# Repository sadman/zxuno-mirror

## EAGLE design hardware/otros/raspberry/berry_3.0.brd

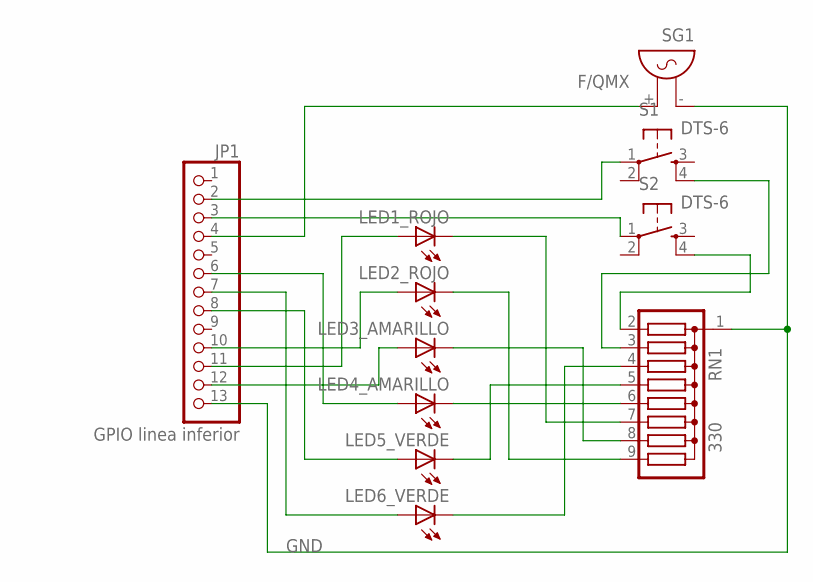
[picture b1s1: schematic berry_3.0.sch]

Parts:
JP1: GPIO linea inferior; 1X13
LED1_ROJO, LED2_ROJO, LED3_AMARILLO, LED4_AMARILLO, LED5_VERDE, LED6_VERDE: LED5MM
RN1: 330; SIL9
S1, S2: DTS-6
SG1: F/QMX

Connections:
GND: JP1.13, RN1.1, SG1.- (1)
unnamed: LED5_VERDE.K (C), RN1.5
unnamed: JP1.2, S1.1
unnamed: LED3_AMARILLO.K (C), RN1.8
unnamed: JP1.10, LED2_ROJO.A
unnamed: LED4_AMARILLO.K (C), RN1.6
unnamed: LED2_ROJO.K (C), RN1.9
unnamed: JP1.4, SG1.+ (2)
unnamed: LED1_ROJO.K (C), RN1.7
unnamed: LED6_VERDE.K (C), RN1.4
unnamed: JP1.7, LED6_VERDE.A
unnamed: JP1.8, LED5_VERDE.A
unnamed: RN1.2, S2.4
unnamed: RN1.3, S1.4
unnamed: JP1.11, LED1_ROJO.A
unnamed: JP1.3, S2.1
unnamed: JP1.6, LED4_AMARILLO.A
unnamed: JP1.12, LED3_AMARILLO.A

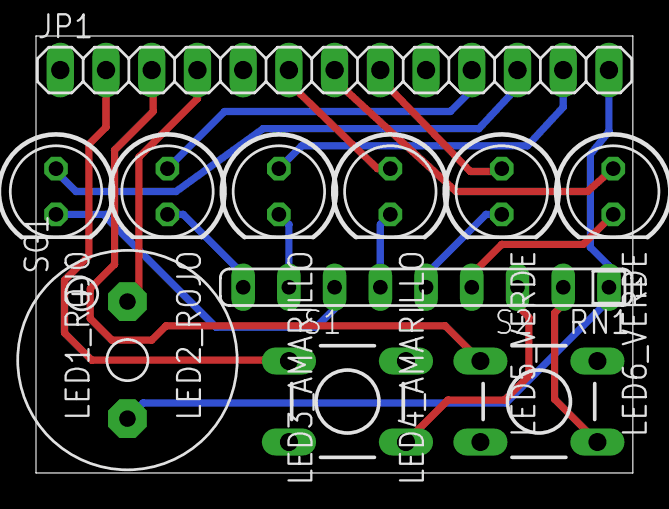
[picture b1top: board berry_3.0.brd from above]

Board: 2 copper layers, 33.2 x 24.3 mm, 11 parts (0 on the bottom side), 18 nets.

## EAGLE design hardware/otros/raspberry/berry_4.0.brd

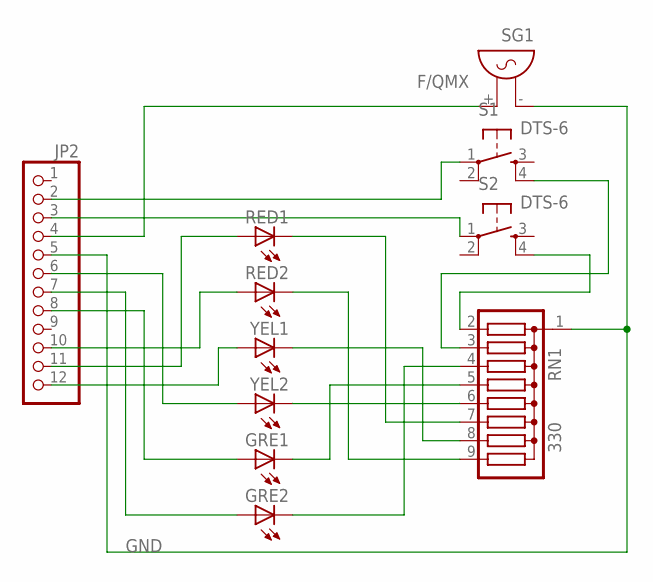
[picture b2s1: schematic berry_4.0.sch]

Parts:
GRE1, GRE2: LED3MM
JP2: PINHD-1X12; 1X12
RED1, RED2: LED3MM
RN1: 330; SIL9
S1, S2: DTS-6
SG1: F/QMX
YEL1, YEL2: LED3MM

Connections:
GND: JP2.5, RN1.1, SG1.- (1)
unnamed: GRE1.K (C), RN1.5
unnamed: JP2.2, S1.1
unnamed: RN1.8, YEL1.K (C)
unnamed: JP2.10, RED2.A
unnamed: RN1.6, YEL2.K (C)
unnamed: RED2.K (C), RN1.9
unnamed: JP2.4, SG1.+ (2)
unnamed: RED1.K (C), RN1.7
unnamed: GRE2.K (C), RN1.4
unnamed: GRE2.A, JP2.7
unnamed: GRE1.A, JP2.8
unnamed: RN1.2, S2.4
unnamed: RN1.3, S1.4
unnamed: JP2.11, RED1.A
unnamed: JP2.3, S2.1
unnamed: JP2.6, YEL2.A
unnamed: JP2.12, YEL1.A

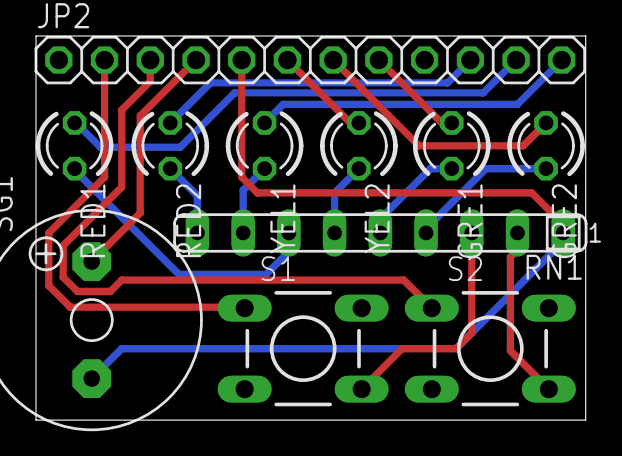
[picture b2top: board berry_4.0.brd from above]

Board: 2 copper layers, 30.5 x 21.3 mm, 11 parts (0 on the bottom side), 18 nets.

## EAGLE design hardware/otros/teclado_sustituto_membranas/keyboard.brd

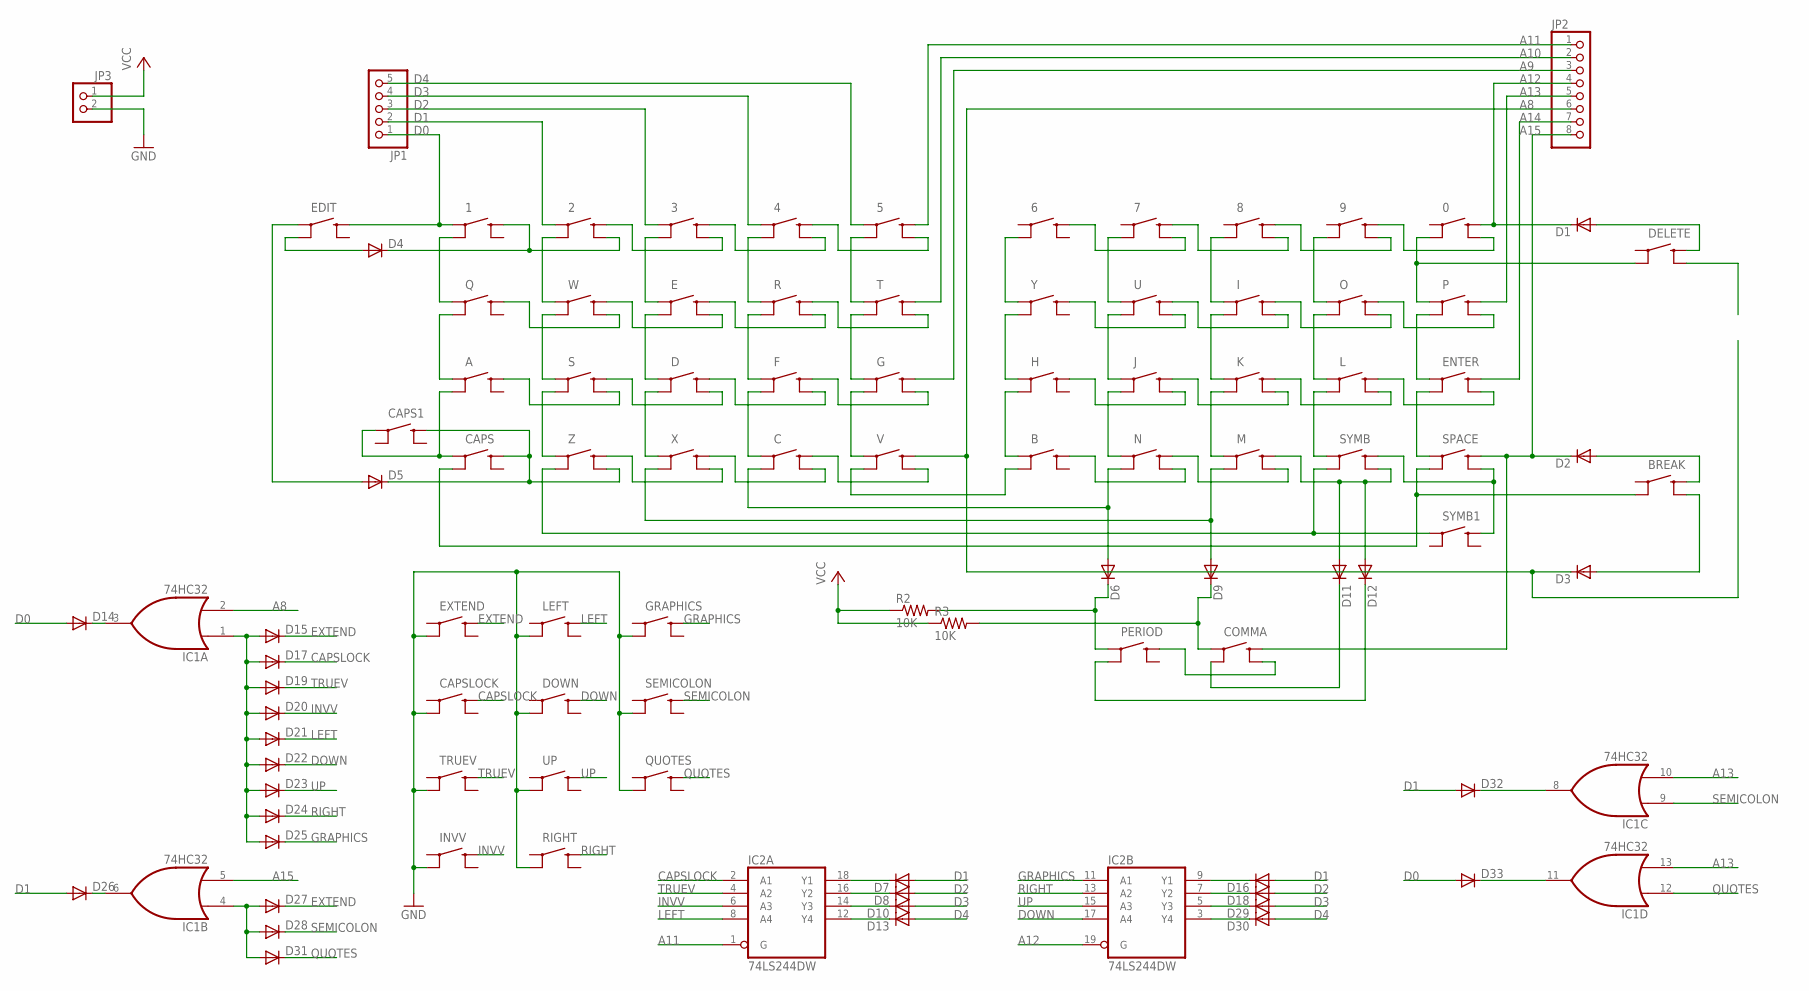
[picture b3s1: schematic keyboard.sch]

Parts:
0, 1, 2, 3, 4, 5, 6, 7, 8, 9: SWITCH-MOMENTARY-2SMD; TACTILE-SWITCH-SMD
A: SWITCH-MOMENTARY-2SMD; TACTILE-SWITCH-SMD
B: SWITCH-MOMENTARY-2SMD; TACTILE-SWITCH-SMD
BREAK: SWITCH-MOMENTARY-2SMD; TACTILE-SWITCH-SMD
C: SWITCH-MOMENTARY-2SMD; TACTILE-SWITCH-SMD
CAPS, CAPS1: SWITCH-MOMENTARY-2SMD; TACTILE-SWITCH-SMD
CAPSLOCK: SWITCH-MOMENTARY-2SMD; TACTILE-SWITCH-SMD
COMMA: SWITCH-MOMENTARY-2SMD; TACTILE-SWITCH-SMD
D: SWITCH-MOMENTARY-2SMD; TACTILE-SWITCH-SMD
D1, D2, D3, D4, D5, D6, D7, D8, D9, D10, D11, D12, D13, D14, D15, D16, D17, D18, D19, D20, D21, D22, D23, D24, D25, D26, D27, D28, D29, D30, D31, D32, D33: DIODE-SOD323-R; SOD323-R
DELETE: SWITCH-MOMENTARY-2SMD; TACTILE-SWITCH-SMD
DOWN: SWITCH-MOMENTARY-2SMD; TACTILE-SWITCH-SMD
E: SWITCH-MOMENTARY-2SMD; TACTILE-SWITCH-SMD
EDIT: SWITCH-MOMENTARY-2SMD; TACTILE-SWITCH-SMD
ENTER: SWITCH-MOMENTARY-2SMD; TACTILE-SWITCH-SMD
EXTEND: SWITCH-MOMENTARY-2SMD; TACTILE-SWITCH-SMD
F: SWITCH-MOMENTARY-2SMD; TACTILE-SWITCH-SMD
G: SWITCH-MOMENTARY-2SMD; TACTILE-SWITCH-SMD
GRAPHICS: SWITCH-MOMENTARY-2SMD; TACTILE-SWITCH-SMD
H: SWITCH-MOMENTARY-2SMD; TACTILE-SWITCH-SMD
I: SWITCH-MOMENTARY-2SMD; TACTILE-SWITCH-SMD
IC1: 74HC32; SO14
IC2: 74LS244DW; SO20W
INVV: SWITCH-MOMENTARY-2SMD; TACTILE-SWITCH-SMD
J: SWITCH-MOMENTARY-2SMD; TACTILE-SWITCH-SMD
JP1: PINHD-1X5; 1X05
JP2: PINHD-1X8; 1X08
JP3: PINHD-1X2; 1X02
K: SWITCH-MOMENTARY-2SMD; TACTILE-SWITCH-SMD
L: SWITCH-MOMENTARY-2SMD; TACTILE-SWITCH-SMD
LEFT: SWITCH-MOMENTARY-2SMD; TACTILE-SWITCH-SMD
M: SWITCH-MOMENTARY-2SMD; TACTILE-SWITCH-SMD
N: SWITCH-MOMENTARY-2SMD; TACTILE-SWITCH-SMD
O: SWITCH-MOMENTARY-2SMD; TACTILE-SWITCH-SMD
P: SWITCH-MOMENTARY-2SMD; TACTILE-SWITCH-SMD
PERIOD: SWITCH-MOMENTARY-2SMD; TACTILE-SWITCH-SMD
Q: SWITCH-MOMENTARY-2SMD; TACTILE-SWITCH-SMD
QUOTES: SWITCH-MOMENTARY-2SMD; TACTILE-SWITCH-SMD
R: SWITCH-MOMENTARY-2SMD; TACTILE-SWITCH-SMD
R2, R3: 10K; M0805
RIGHT: SWITCH-MOMENTARY-2SMD; TACTILE-SWITCH-SMD
S: SWITCH-MOMENTARY-2SMD; TACTILE-SWITCH-SMD
SEMICOLON: SWITCH-MOMENTARY-2SMD; TACTILE-SWITCH-SMD
SPACE: SWITCH-MOMENTARY-2SMD; TACTILE-SWITCH-SMD
SYMB, SYMB1: SWITCH-MOMENTARY-2SMD; TACTILE-SWITCH-SMD
T: SWITCH-MOMENTARY-2SMD; TACTILE-SWITCH-SMD
TRUEV: SWITCH-MOMENTARY-2SMD; TACTILE-SWITCH-SMD
U: SWITCH-MOMENTARY-2SMD; TACTILE-SWITCH-SMD
UP: SWITCH-MOMENTARY-2SMD; TACTILE-SWITCH-SMD
V: SWITCH-MOMENTARY-2SMD; TACTILE-SWITCH-SMD
W: SWITCH-MOMENTARY-2SMD; TACTILE-SWITCH-SMD
X: SWITCH-MOMENTARY-2SMD; TACTILE-SWITCH-SMD
Y: SWITCH-MOMENTARY-2SMD; TACTILE-SWITCH-SMD
Z: SWITCH-MOMENTARY-2SMD; TACTILE-SWITCH-SMD

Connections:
A8: D3.C, IC1.2 (I1), JP2.6, V.3 (2)
A9: G.3 (2), JP2.3
A10: JP2.2, T.3 (2)
A11: 5.3 (2), IC2.1 (G), JP2.1
A12: 0.3 (2), D1.C, IC2.19 (G), JP2.4
A13: IC1.10 (I1), IC1.13 (I1), JP2.5, P.3 (2)
A14: ENTER.3 (2), JP2.7
A15: COMMA.3 (2), D2.C, IC1.5 (I1), JP2.8, SPACE.3 (2)
CAPSLOCK: CAPSLOCK.3 (2), D17.C, IC2.2 (A1)
D0: 1.1, D14.A, D33.A, EDIT.3 (2), JP1.1
D1: 2.1, D7.A, D16.A, D26.A, D32.A, JP1.2
D2: 3.1, D8.A, D18.A, JP1.3
D3: 4.1, D10.A, D29.A, JP1.4
D4: 5.1, D13.A, D30.A, JP1.5
DOWN: D22.C, DOWN.3 (2), IC2.17 (A4)
EXTEND: D15.C, D27.C, EXTEND.3 (2)
GND: CAPSLOCK.2 (3), DOWN.2 (3), EXTEND.2 (3), GRAPHICS.2 (3), IC1.7 (GND), IC2.10 (GND), INVV.2 (3), JP3.2, LEFT.2 (3), QUOTES.2 (3), RIGHT.2 (3), SEMICOLON.2 (3), TRUEV.2 (3), UP.2 (3)
GRAPHICS: D25.C, GRAPHICS.3 (2), IC2.11 (A1)
INVV: D20.C, IC2.6 (A3), INVV.3 (2)
LEFT: D21.C, IC2.8 (A4), LEFT.3 (2)
unnamed: D4.A, EDIT.2 (3)
unnamed: D5.A, EDIT.1
unnamed: BREAK.3 (2), D2.A
unnamed: BREAK.4, D3.A
unnamed: D1.A, DELETE.3 (2)
unnamed: 1.2 (3), Q.1
unnamed: A.1, Q.2 (3)
unnamed: A.2 (3), CAPS.1, CAPS1.1
unnamed: BREAK.2 (3), CAPS.2 (3), SPACE.2 (3)
unnamed: B.1, H.2 (3)
unnamed: H.1, Y.2 (3)
unnamed: 6.2 (3), Y.1
unnamed: 2.2 (3), W.1
unnamed: S.1, W.2 (3)
unnamed: S.2 (3), Z.1
unnamed: SYMB.2 (3), SYMB1.1, Z.2 (3)
unnamed: D9.A, M.2 (3), X.2 (3)
unnamed: C.2 (3), D6.A, N.2 (3)
unnamed: B.2 (3), V.2 (3)
unnamed: 3.2 (3), E.1
unnamed: D.1, E.2 (3)
unnamed: D.2 (3), X.1
unnamed: 4.2 (3), R.1
unnamed: F.1, R.2 (3)
unnamed: C.1, F.2 (3)
unnamed: 5.2 (3), T.1
unnamed: G.1, T.2 (3)
unnamed: G.2 (3), V.1
unnamed: 3.3 (2), 4.4
unnamed: 4.3 (2), 5.4
unnamed: 2.3 (2), 3.4
unnamed: 1.3 (2), 2.4, D4.C
unnamed: C.3 (2), V.4
unnamed: R.3 (2), T.4
unnamed: E.3 (2), R.4
unnamed: E.4, W.3 (2)
unnamed: Q.3 (2), W.4
unnamed: F.3 (2), G.4
unnamed: D.3 (2), F.4
unnamed: D.4, S.3 (2)
unnamed: A.3 (2), S.4
unnamed: 0.4, 9.3 (2)
unnamed: J.2 (3), N.1
unnamed: J.1, U.2 (3)
unnamed: 7.2 (3), U.1
unnamed: K.2 (3), M.1
unnamed: I.2 (3), K.1
unnamed: 8.2 (3), I.1
unnamed: L.2 (3), SYMB.1
unnamed: L.1, O.2 (3)
unnamed: 9.2 (3), O.1
unnamed: ENTER.2 (3), SPACE.1
unnamed: ENTER.1, P.2 (3)
unnamed: 0.2 (3), DELETE.2 (3), P.1
unnamed: 8.3 (2), 9.4
unnamed: 7.3 (2), 8.4
unnamed: 6.3 (2), 7.4
unnamed: C.4, X.3 (2)
unnamed: X.4, Z.3 (2)
unnamed: CAPS.3 (2), CAPS1.3 (2), D5.C, Z.4
unnamed: O.3 (2), P.4
unnamed: I.3 (2), O.4
unnamed: I.4, U.3 (2)
unnamed: U.4, Y.3 (2)
unnamed: ENTER.4, L.3 (2)
unnamed: K.3 (2), L.4
unnamed: J.3 (2), K.4
unnamed: H.3 (2), J.4
unnamed: SPACE.4, SYMB.3 (2), SYMB1.3 (2)
unnamed: D11.A, D12.A, M.3 (2), SYMB.4
unnamed: M.4, N.3 (2)
unnamed: B.3 (2), N.4
unnamed: D7.C, IC2.18 (Y1)
unnamed: D8.C, IC2.16 (Y2)
unnamed: COMMA.4, PERIOD.3 (2)
unnamed: D10.C, IC2.14 (Y3)
unnamed: COMMA.2 (3), D11.C
unnamed: D12.C, PERIOD.2 (3)
unnamed: D13.C, IC2.12 (Y4)
unnamed: D16.C, IC2.9 (Y1)
unnamed: D6.C, PERIOD.1, R2.2
unnamed: COMMA.1, D9.C, R3.2
unnamed: D14.C, IC1.3 (O)
unnamed: D18.C, IC2.7 (Y2)
unnamed: D26.C, IC1.6 (O)
unnamed: D27.A, D28.A, D31.A, IC1.4 (I0)
unnamed: D29.C, IC2.5 (Y3)
unnamed: D30.C, IC2.3 (Y4)
unnamed: D15.A, D17.A, D19.A, D20.A, D21.A, D22.A, D23.A, D24.A, D25.A, IC1.1 (I0)
unnamed: D32.C, IC1.8 (O)
unnamed: D33.C, IC1.11 (O)
QUOTES: D31.C, IC1.12 (I0), QUOTES.3 (2)
RIGHT: D24.C, IC2.13 (A2), RIGHT.3 (2)
SEMICOLON: D28.C, IC1.9 (I0), SEMICOLON.3 (2)
TRUEV: D19.C, IC2.4 (A2), TRUEV.3 (2)
UP: D23.C, IC2.15 (A3), UP.3 (2)
VCC: IC1.14 (VCC), IC2.20 (VCC), JP3.1, R2.1, R3.1

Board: 2 copper layers, 98 parts (58 on the bottom side), 117 nets, no tracks yet.

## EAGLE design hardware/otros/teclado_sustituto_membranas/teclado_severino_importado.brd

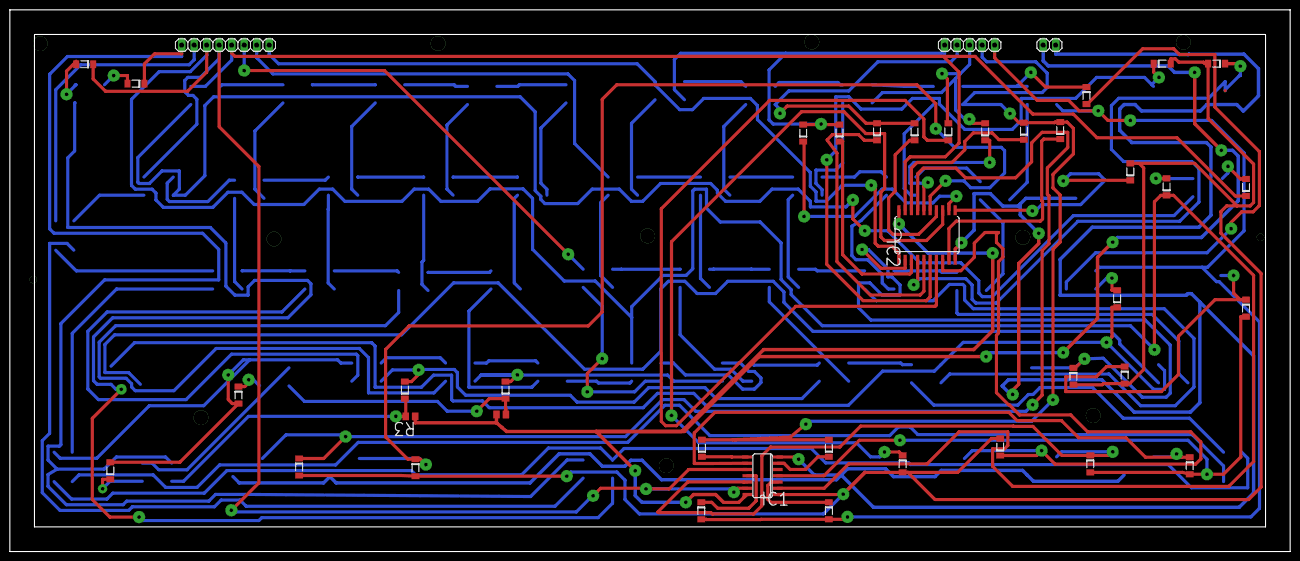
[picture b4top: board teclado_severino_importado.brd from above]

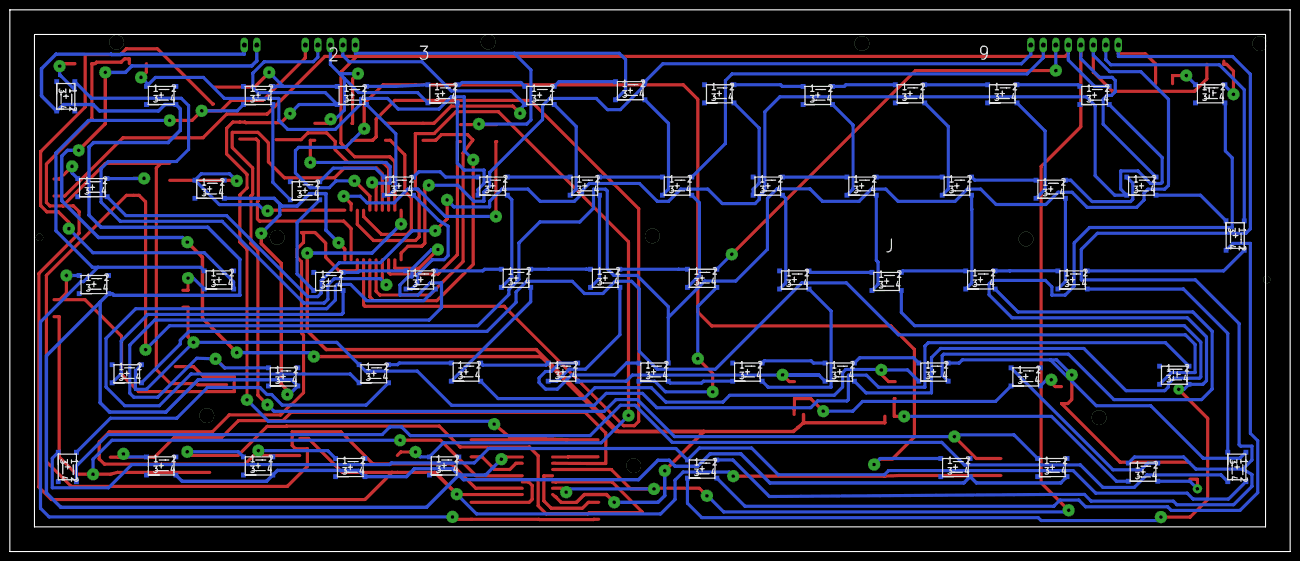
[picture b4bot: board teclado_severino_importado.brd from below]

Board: 2 copper layers, 260.0 x 110.0 mm, 111 parts (58 on the bottom side), 116 nets.

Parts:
0, 1, 2, 3, 4, 5, 6, 7, 8, 9, ._PERIOD_: B3F-40XX_2PRIMARY
,_COMMA_: B3F-40XX_2PRIMARY
A: B3F-40XX_2PRIMARY
B: B3F-40XX_2PRIMARY
BREAK: MINISWITCH_SMD_1PRIMARY
C: B3F-40XX_2PRIMARY
CAPS: MINISWITCH_SMD_1PRIMARY
CAPS1: B3F-40XX_2PRIMARY
CAPSLOCK: B3F-40XX_2PRIMARY
D: B3F-40XX_2PRIMARY
D1, D2, D3, D4, D5, D6, D7, D8, D9, D10, D11, D12, D13, D14, D15, D16, D17, D18, D19, D20, D21, D22, D23, D24, D25, D26, D27, D28, D29, D30, D31, D32, D33: MELF-D3512-1405_1PRIMARY
DELETE: B3F-40XX_2PRIMARY
DEXTRA: MELF-D3512-1405_1PRIMARY
DOWN: B3F-40XX_2PRIMARY
DUMMY1, DUMMY2: P:EX59Y59D591
DUMMY3, DUMMY4, DUMMY5, DUMMY6, DUMMY7, DUMMY8, DUMMY9, DUMMY10, DUMMY11, DUMMY12: P:EX118Y118D1181
E: B3F-40XX_2PRIMARY
EDIT: B3F-40XX_2PRIMARY
ENTER: B3F-40XX_1PRIMARY
EXTEND: B3F-40XX_2PRIMARY
F: B3F-40XX_2PRIMARY
G: B3F-40XX_2PRIMARY
GRAPHICS: B3F-40XX_2PRIMARY
H: B3F-40XX_2PRIMARY
I: B3F-40XX_2PRIMARY
IC1: 74HC32; SO14_1PRIMARY
IC2: 74LS244DW; SO20W_1PRIMARY
INVV: B3F-40XX_2PRIMARY
J: B3F-40XX_2PRIMARY
JP1: 1X05_1PRIMARY
JP2: 1X08_1PRIMARY
JP3: 1X02_1PRIMARY
K: B3F-40XX_2PRIMARY
L: B3F-40XX_2PRIMARY
LEFT: B3F-40XX_2PRIMARY
M: B3F-40XX_2PRIMARY
N: B3F-40XX_2PRIMARY
O: B3F-40XX_2PRIMARY
P: B3F-40XX_2PRIMARY
Q: B3F-40XX_2PRIMARY
QUOTES: B3F-40XX_2PRIMARY
R: B3F-40XX_2PRIMARY
R2, R3: 10K; M0805_1PRIMARY
RIGHT: B3F-40XX_2PRIMARY
S: B3F-40XX_2PRIMARY
SEMICOLON: B3F-40XX_2PRIMARY
SPACE: B3F-40XX_2PRIMARY
SYMB, SYMB1: B3F-40XX_1PRIMARY
T: B3F-40XX_2PRIMARY
TRUEV: B3F-40XX_1PRIMARY
U: B3F-40XX_2PRIMARY
UP: B3F-40XX_2PRIMARY
V: B3F-40XX_2PRIMARY
W: B3F-40XX_2PRIMARY
X: B3F-40XX_2PRIMARY
Y: B3F-40XX_2PRIMARY
Z: B3F-40XX_2PRIMARY

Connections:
A8: D3.2, DEXTRA.2, IC1.2, JP2.6, V.2
A9: G.2, JP2.3
A10: JP2.2, T.2
A11: 5.2, IC2.1, JP2.1
A12: 0.2, D1.2, IC2.19, JP2.4
A13: IC1.10, IC1.13, JP2.5, P.2
A14: ENTER.1, JP2.7
CAPSLOCK: CAPSLOCK.1, D17.2, IC2.2
D0: 1.3, D14.1, D33.1, EDIT.1, JP1.1
D1: 2.3, D7.1, D16.1, D26.1, D32.1, JP1.2
D2: 3.3, D8.1, D18.1, JP1.3
D3: 4.3, D10.1, D29.1, JP1.4
D4: 5.3, D13.1, D30.1, JP1.5
DOWN: D22.2, DOWN.1, IC2.17
EXTEND: D15.2, D27.2, EXTEND.1
GND: CAPSLOCK.4, DOWN.4, EXTEND.4, GRAPHICS.4, IC1.7, IC2.10, INVV.4, JP3.2, LEFT.4, QUOTES.4, RIGHT.4, SEMICOLON.4, TRUEV.4, UP.4
GRAPHICS: D25.2, GRAPHICS.1, IC2.11
INVV: D20.2, IC2.6, INVV.1
LEFT: D21.2, IC2.8, LEFT.1
NET0_1: 0.1, 9.2
NET0_4: 0.4, DELETE.4, P.3
NET1_2: 1.2, 2.1, D4.2
NET1_4: 1.4, Q.3
NET2_2: 2.2, 3.1
NET2_4: 2.4, W.3
NET3_2: 3.2, 4.1
NET3_4: 3.4, E.3
NET4_2: 4.2, 5.1
NET4_4: 4.4, R.3
NET5_4: 5.4, T.3
NET6_2: 6.2, 7.1
NET6_4: 6.4, Y.3
NET7_2: 7.2, 8.1
NET7_4: 7.4, U.3
NET8_2: 8.2, 9.1
NET8_4: 8.4, I.3
NET9_4: 9.4, O.3
NET,_COMMA__2: ,_COMMA_.2, ._PERIOD_.1
NET,_COMMA__3: ,_COMMA_.3, D9.2, R3.2
NET,_COMMA__4: ,_COMMA_.4, D11.2
NET._PERIOD__3: ._PERIOD_.3, D6.2, R2.2
NET._PERIOD__4: ._PERIOD_.4, D12.2
NETA_2: A.2, S.1
NETA_3: A.3, Q.4
NETA_4: A.4, CAPS1.3
NETB_2: B.2, N.1
NETB_3: B.3, V.4
NETB_4: B.4, H.4
NETCAPS1_2: CAPS1.2, Z.1
NETC_1: C.1, X.2
NETC_2: C.2, V.1
NETC_3: C.3, F.4
NETC_4: C.4, D6.1, N.3
NETD1_A: D1.1, DELETE.1
NETD4_A: D4.1, EDIT.4
NETD5_A: D5.1, EDIT.3
NETD7_C: D7.2, IC2.18
NETD8_C: D8.2, IC2.16
NETD9_A: D9.1, M.3, X.4
NETD10_C: D10.2, IC2.14
NETD11_A: D11.1, D12.1, M.2, SYMB.1
NETD13_C: D13.2, IC2.12
NETD14_C: D14.2, IC1.3
NETD15_A: D15.1, D17.1, D19.1, D20.1, D21.1, D22.1, D23.1, D24.1, D25.1, IC1.1
NETD16_C: D16.2, IC2.9
NETD18_C: D18.2, IC2.7
NETD26_C: D26.2, IC1.6
NETD27_A: D27.1, D28.1, D31.1, IC1.4
NETD29_C: D29.2, IC2.5
NETD30_C: D30.2, IC2.3
NETD32_C: D32.2, IC1.8
NETD33_C: D33.2, IC1.11
NETDELETE_2: DELETE.2, DEXTRA.1
NETD_1: D.1, S.2
NETD_2: D.2, F.1
NETD_3: D.3, E.4
NETD_4: D.4, X.3
NETENTER_2: ENTER.2, L.2
NETENTER_3: ENTER.3, P.4
NETENTER_4: ENTER.4, SPACE.4
NETE_1: E.1, W.2
NETE_2: E.2, R.1
NETF_2: F.2, G.1
NETF_3: F.3, R.4
NETG_3: G.3, T.4
NETG_4: G.4, V.3
NETH_2: H.2, J.1
NETH_3: H.3, Y.4
NETI_1: I.1, U.2
NETI_2: I.2, O.1
NETI_4: I.4, K.3
NETJ_2: J.2, K.1
NETJ_3: J.3, U.4
NETJ_4: J.4, N.4
NETK_2: K.2, L.1
NETK_4: K.4, M.4
NETL_3: L.3, O.4
NETL_4: L.4, SYMB.3
NETM_1: M.1, N.2
NETO_2: O.2, P.1
NETQ_2: Q.2, W.1
NETR_2: R.2, T.1
NETSPACE_1: SPACE.1, SYMB.2, SYMB1.3
NETSYMB1_1: SYMB1.1, Z.4
NETSYMB1_2: SYMB.4, SYMB1.2
NETS_3: S.3, W.4
NETS_4: S.4, Z.3
NETU_1: U.1, Y.2
NETX_1: X.1, Z.2
QUOTES: D31.2, IC1.12, QUOTES.1
RIGHT: D24.2, IC2.13, RIGHT.1
SEMICOLON: D28.2, IC1.9, SEMICOLON.1
TRUEV: D19.2, IC2.4, TRUEV.1
UP: D23.2, IC2.15, UP.1
VCC: IC1.14, IC2.20, JP3.1, R2.1, R3.1
VET: ,_COMMA_.1, D2.2, JP2.8, SPACE.2

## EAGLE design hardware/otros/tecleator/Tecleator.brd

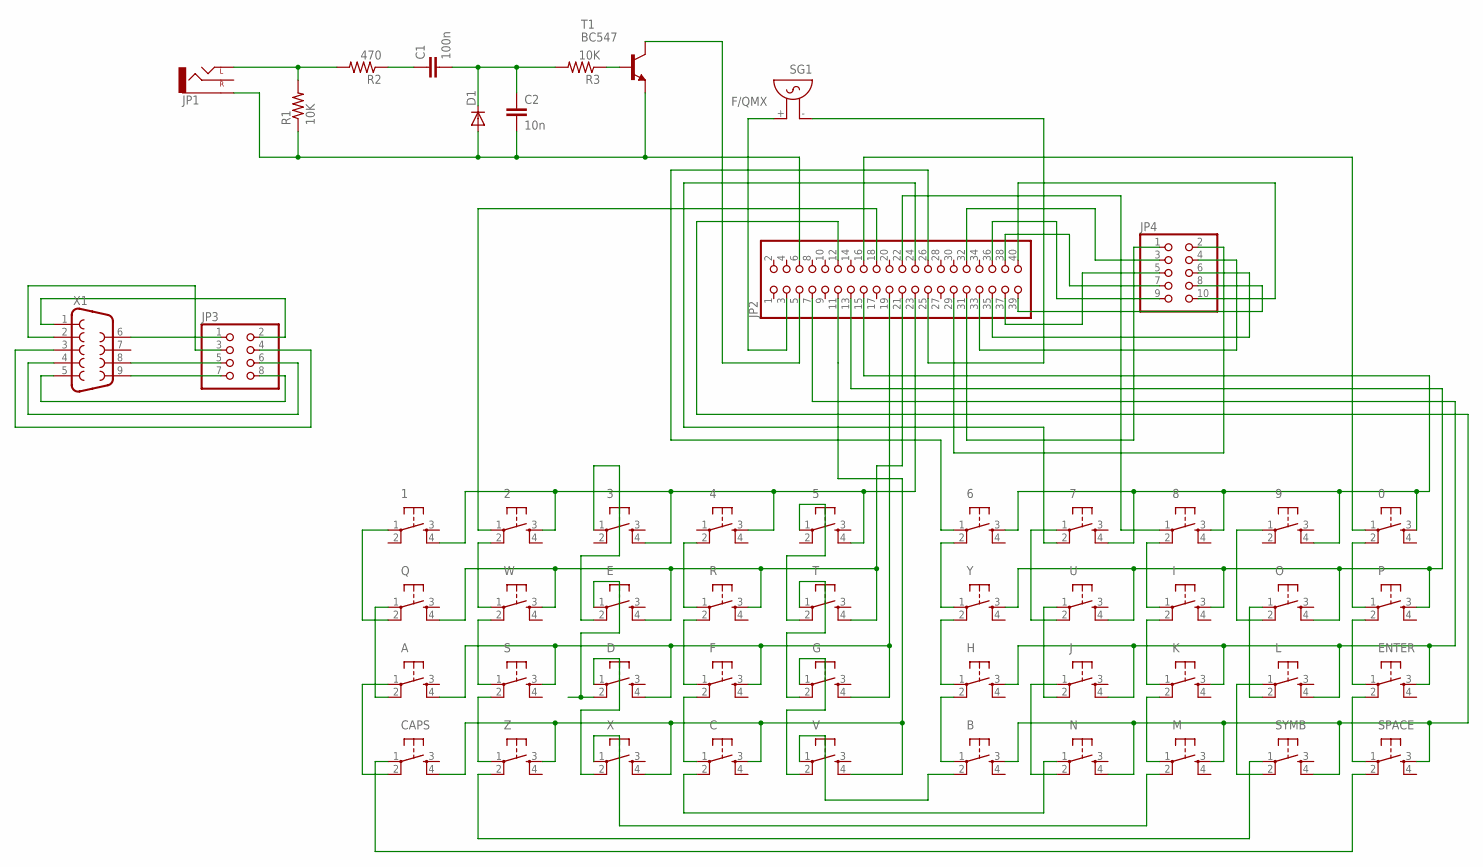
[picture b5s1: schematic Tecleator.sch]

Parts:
0, 1, 2, 3, 4, 5, 6, 7, 8, 9: DTS-6
A: DTS-6
B: DTS-6
C: DTS-6
C1: 100n; C050-025X075
C2: 10n; C050-025X075
CAPS: DTS-6
D: DTS-6
D1: DIODE-DO41-7.6; DO41-7.6
E: DTS-6
ENTER: DTS-6
F: DTS-6
G: DTS-6
H: DTS-6
I: DTS-6
J: DTS-6
JP1: AUDIO-JACKPTH; AUDIO-JACK
JP2: PINHD-2X20; 2X20
JP3: PINHD-2X4; 2X04
JP4: PINHD-2X5; 2X05
K: DTS-6
L: DTS-6
M: DTS-6
N: DTS-6
O: DTS-6
P: DTS-6
Q: DTS-6
R: DTS-6
R1, R3: 10K; 0204/7
R2: 470; 0204/7
S: DTS-6
SG1: F/QMX
SPACE: DTS-6
SYMB: DTS-6
T: DTS-6
T1: BC547; TO92
U: DTS-6
V: DTS-6
W: DTS-6
X: DTS-6
X1: DB9MALE; DB9_MALE
Y: DTS-6
Z: DTS-6

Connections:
A9: A.4, D.4, F.3, G.4, JP2.19, S.3
A10: E.4, JP2.21, Q.4, R.3, T.4, W.3
A11: 1.4, 2.3, 3.4, 4.3, 5.4, JP2.23
A12: 0.3, 6.3, 7.4, 8.3, 9.4, JP2.15
A13: I.3, JP2.13, O.4, P.3, U.4, Y.3
A14: ENTER.3, H.3, J.4, JP2.7, K.3, L.4
D1: 2.1, JP2.18
D2: 8.1, JP2.22
D3: 7.2, JP2.24
D4: 6.1, JP2.26
ELETE: M.2, X.1
unnamed: CAPS.1, SPACE.2
unnamed: 1.1, Q.2
unnamed: K.2, M.1
unnamed: C2.2, D1.A, JP1.SLEEVE, JP2.6, R1.1, T1.1 (E)
unnamed: JP1.TIP (LEFT), R1.2, R2.2
unnamed: 0.1, JP2.16
unnamed: A.2, Q.1
unnamed: C1.1, R2.1
unnamed: A.1, CAPS.2
unnamed: B.1, H.2
unnamed: H.1, Y.2
unnamed: 6.2, Y.1
unnamed: 3.1, E.2
unnamed: S.1, W.2
unnamed: S.2, Z.1
unnamed: SYMB.1, Z.2
unnamed: 5.1, T.2
unnamed: 7.1, U.2
unnamed: B.2, V.1
unnamed: JP2.39, JP4.8
unnamed: JP2.3, SG1.+ (2)
unnamed: G.2, T.1
unnamed: 4.2, R.1
unnamed: F.1, R.2
unnamed: C.1, F.2
unnamed: G.1, V.2
unnamed: J.2, U.1
unnamed: J.1, N.2
unnamed: C.3, CAPS.4, JP2.11, V.4, X.4, Z.3
unnamed: JP2.25, SG1.- (1)
unnamed: D.2, E.1
unnamed: 2.2, W.1
unnamed: JP2.37, JP4.5
unnamed: JP2.40, JP4.10
unnamed: JP2.36, JP4.9
unnamed: JP2.38, JP4.7
unnamed: JP2.33, JP4.4
unnamed: JP2.32, JP4.3
unnamed: JP2.29, JP4.2
unnamed: JP2.35, JP4.6
unnamed: JP3.5, X1.8
unnamed: JP2.31, JP4.1
unnamed: C.2, N.1
unnamed: L.1, SYMB.2
unnamed: 9.1, O.2
unnamed: JP3.6, X1.4
unnamed: I.2, K.1
unnamed: 8.2, I.1
unnamed: L.2, O.1
unnamed: JP3.1, X1.6
unnamed: JP3.2, X1.1
unnamed: ENTER.2, SPACE.1
unnamed: ENTER.1, P.2
unnamed: 0.2, P.1
unnamed: JP3.3, X1.2
unnamed: JP3.8, X1.5
unnamed: JP3.7, X1.9
unnamed: JP3.4, X1.3
unnamed: C1.2, C2.1, D1.C, R3.2
unnamed: R3.1, T1.2 (B)
unnamed: JP2.5, T1.3 (C)
unnamed: D.1, X.2
VET: B.3, JP2.12, M.3, N.4, SPACE.3, SYMB.4

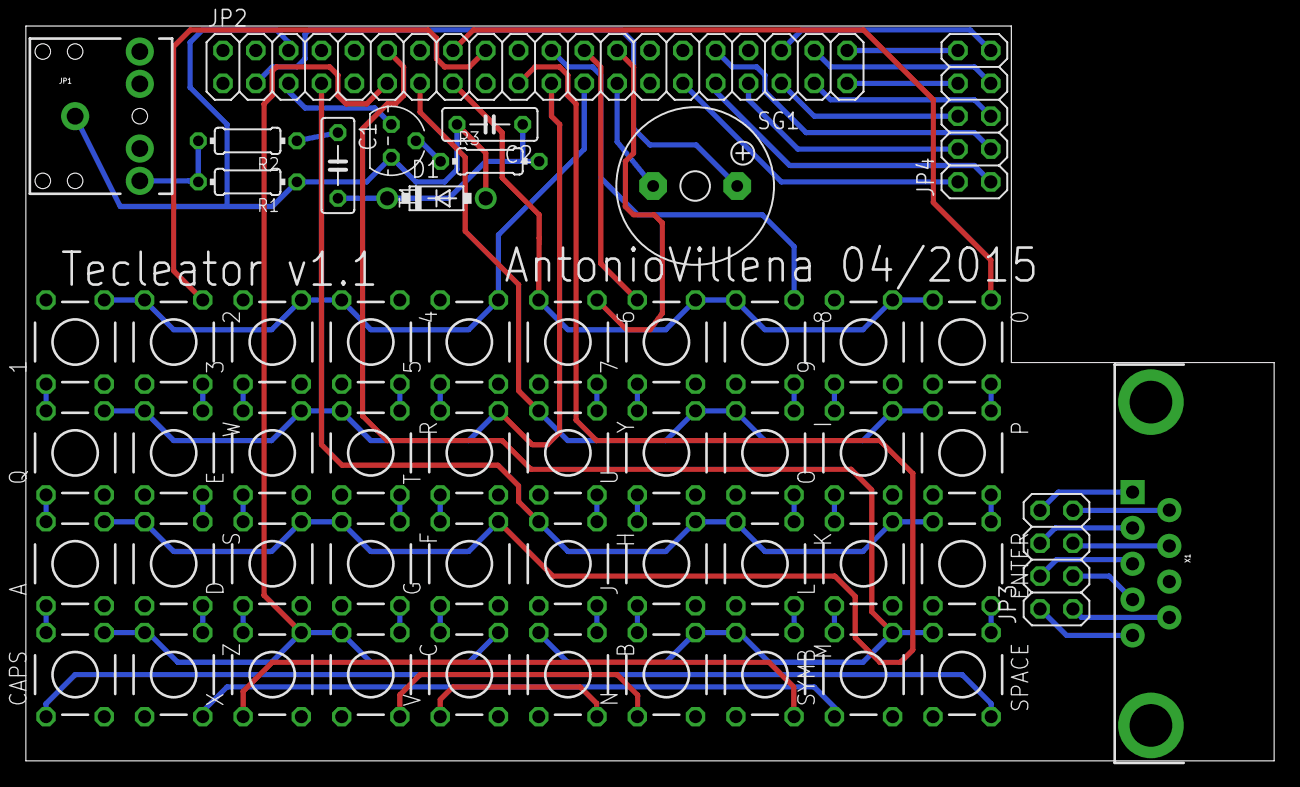
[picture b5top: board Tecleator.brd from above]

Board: 2 copper layers, 96.5 x 56.8 mm, 53 parts (0 on the bottom side), 74 nets.

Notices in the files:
parts and their libraries:
SparkFun-Electromechanical: Licensing: Creative Commons ShareAlike 4.0 International - https://creativecommons.org/licenses/by-sa/4.0
